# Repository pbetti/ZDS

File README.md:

# ZDS

What you find here are all my stuff about Nuova Elettronica Z80. Software, ideas &amp; projects, both software and hardware.
See more at http://www.z80cpu.eu/projects/14-data-articles/116-z80ne-where-it-all-began

Microcomputer Z80 by Nuova Elettronica

The system consists of dedicated boards. Each card performs a specific function and all the main boards are connected on a propietary bus.
As i found out later, the original design of the system was effectively developed by a company called Micro Design of Genoa and not by Nuova Elettronica.
The orientation however, is to provide an educational system as evidenced by the basic system that consists of the CPU board and an hexadecimal keyboard.
The magazine, however, has introduced later a comprehensive set of additional hardware to allow the construction of a complete system of a level comparable to systems like S-100s or TRS-80 just for an example.
The kits provided by Nuova Elettronica were presented fairly quickly at the beginning and then slow down over time.
The whole system is developed, however, covering a period of considerably long time from 1979 to 1985, which is much greater in life expectancy then today's PC.
The decision to break up the presentation and furniture of the Z80NE hardware, worked well for both the magazine, interested in selling kits and so to maintains high the interest in his system, both for the users who can spread over time the costs (quite remarkable at the end) of buying the whole system and, at the same time, having the time to "assimilate" what the magazine continues to offer in terms of didactic information a kit after another.

The board design is sophisticated and robust, with low component density so to put even the less "technically savvy" people able to mount the components without errors (well... almost).
As to be noticed, not all the hardware presented can be used simultaneously, for example, there are two video interfaces, a low resolution and a hi-res which are mutually incompatible, as well as various memory cards that can only be used in certain configurations to obtain a maximum of up to 56K of RAM which is the limit for our computer. This is because the upper 4kbytes are used by the monitor and lower 4k of RAM (a single kbyte used actually) from E000H to EFFFH is reserved for the lo-res video card.
Another interesting case is the system monitor originally present on the CPU board, which maps 1kb of EPROM at address 8000H, thus blocking any expansion above 32k, chip that infact was removed almost immediately, and placed on the floppy interface card (mapped at F000H).

This apparent schizophrenic design is explained, over the time, with the intent to have a system that users can set up accordingly to their needs and interests.
Even if, i'm willing to bet that the most of them have brought their Z80NE to its maximum potential.
Many of these limitations can easily be overcome with small interventions, as we'll see later.

The system BUS is parallel, consisting of 48 lines divided on two single-in-line connectors of 24 pins each.
The connector "A" drives power (-12V, + 12V, + 5V) and all control signals of Z80 cpu including IEI, IEO pins that should established a daisy-chain interrupt priority between the cards according to the position of insertion, feature never used by Nuova Elettronica, while the connector "B" was dedicated to the address and data lines.

Normally, the power supply and the boards were enclosed in a 5U rack mount black case. This all-black style led me to give to my system the nickname of Z80Darkstar, for which you'll find references in the next articles.

For all details about every board and also original schematics and magazine articles, please, look here: http://www.z80ne.com/eng/hardware.asp

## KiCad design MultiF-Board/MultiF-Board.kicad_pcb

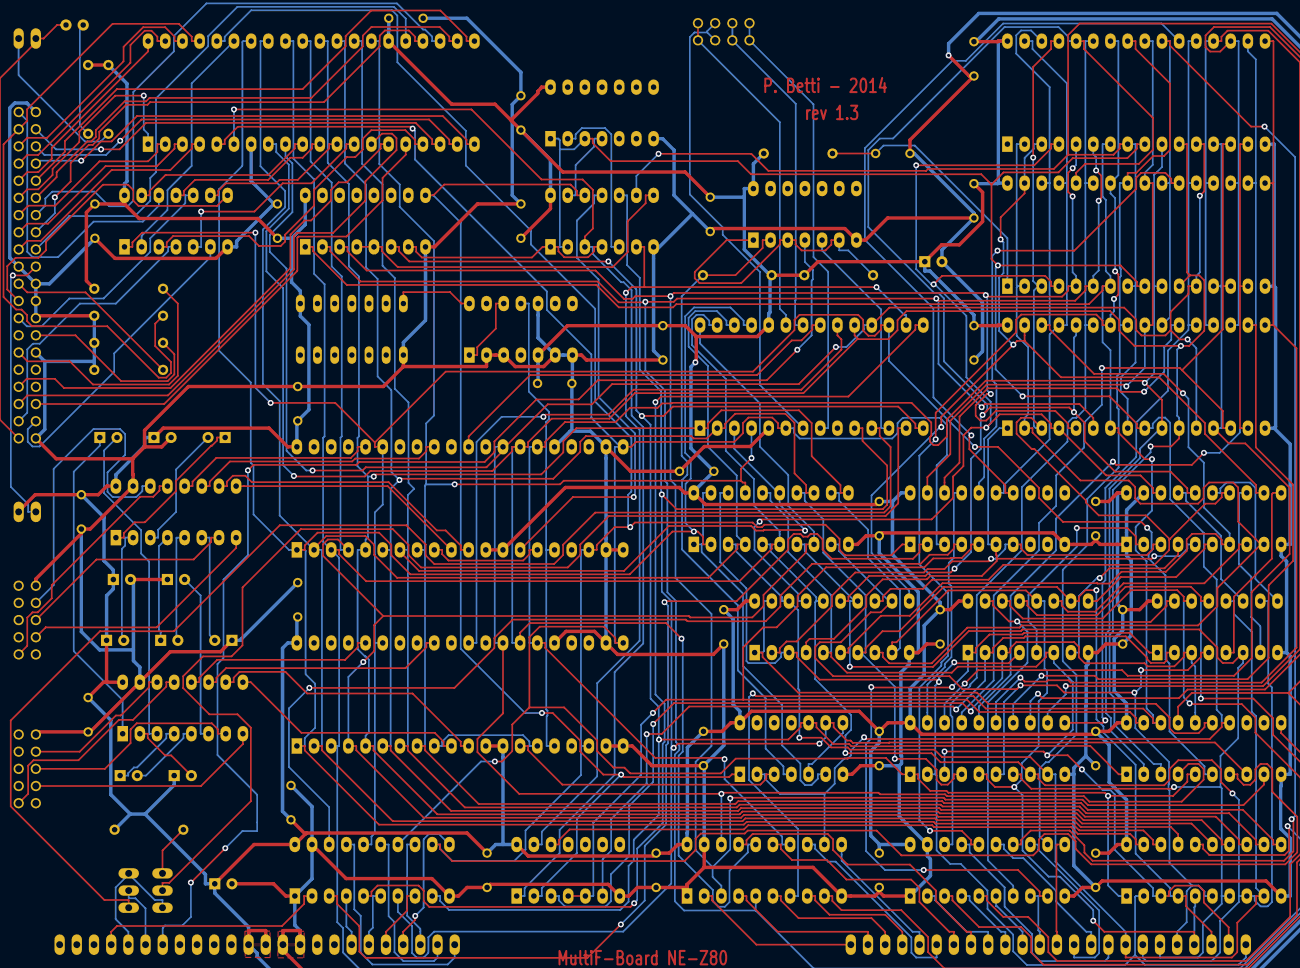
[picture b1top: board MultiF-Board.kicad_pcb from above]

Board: 2 copper layers, 93 parts (0 on the bottom side), 198 nets.

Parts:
C1, C2, C3, C4, C5, C6, C7, C8, C9, C10: 1.0 uF; C1V8
C11, C42: 10 uF; C1V8
C12, C13, C14, C15, C16, C17, C18, C19, C20, C21, C22, C23, C24, C25, C26, C27, C28, C29, C30, C31, C32, C33, C34, C35, C36, C37, C38, C39, C40: 0.1; C2
C41: 0.047; C2
D1: IDE_LED; LED-3MM
JP1, JP2: PINHD-1X3; pinhead-1-1X03
JP3: IDE_VCC; pinhead-1-1X02
JP5: PINHD-2X4; pinhead-1-2X04
JPA1: PINHD-1X24; pinhead-1-1X24
JPB1: PINHD-1X24; pinhead-1-1X24
P1: SERIAL1; pinhead-1-2X05
P2: SERIAL2; pinhead-1-2X05
P3: IDE; pinhead-1-2X20
P4: IDE_LED; pinhead-1-1X02
QG1: OSC; oldchips-DIL14
R1, R8, R9: 3300; R4
R2, R3, R4, R5: 10k; R4
R6, R7: 470; R4
R10: 330; R4
U1, U6: 74LS14; DIP-14__300_ELL
U2: 8255; DIP-40__600_ELL
U3, U4, U5, U15, U27: 74LS244; DIP-20__300_ELL
U7, U22: 74LS32; DIP-14__300_ELL
U8: 74LS11; DIP-14__300_ELL
U9, U13: 74LS245; DIP-20__300_ELL
U10: MMU_GAL; DIP-20__300_ELL
U11, U12: 7489; DIP-16__300_ELL
U14: 74LS90; DIP-14__300_ELL
U16: 74LS240; DIP-20__300_ELL
U17, U26: TI16550; DIP-40__600_ELL
U18, U21: SRAM_512K; DIP-32__600_ELL
U19: 74LS138; DIP-16__300_ELL
U20, U29: MAX-232; DIP-16__300_ELL
U23: MEM_GAL; DIP-20__300_ELL
U24: 74LS06; DIP-14__300_ELL
U25: 29EE020; DIP-32__600_ELL
U28: Z80-CTC; DIP-28__600_ELL

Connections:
+5V: C3.1, C4.1, C8.1, C9.1, C11.1, C12.1, C13.1, C14.1, C15.1, C16.1, C17.1, C18.1, C19.1, C20.1, C21.1, C22.1, C23.1, C24.1, C25.1, C26.1, C27.1, C28.1, C29.1, C30.1, C31.1, C32.1, C33.1, C34.1, C35.1, C36.1, C37.1, C38.1, C39.1, C40.1, C42.1, JP3.1, JPA1.12, JPA1.13, QG1.14, R1.1, R2.1, R6.2, R7.2, R8.2, R9.1, R10.1, U1.14, U2.26, U3.20, U4.20, U5.20, U6.14, U7.14, U8.14, U9.20, U10.20, U11.16, U12.16, U13.20, U14.5, U15.20, U16.20, U17.12, U17.13, U17.40, U18.32, U19.16, U20.16, U21.32, U22.14, U23.20, U24.14, U25.32, U26.12, U26.13, U26.40, U27.20, U28.24, U29.16
//ESR1: U17.14, U22.3
//ESR2: U7.11, U26.14
//E_CTC: U7.6, U8.13, U28.16
//E_IDE: U2.6, U7.3, U8.1
//E_SER: U7.12, U8.2, U19.9, U22.1
//IDECTC: U7.1, U7.4, U19.7
//INT: JPA1.7, U24.4
//ISR: R8.1, U22.4, U24.2
//MBUSEN: U9.19, U23.17
//MENA: U8.4, U8.5, U10.19, U23.5
//MME: U8.6, U11.2, U12.2
//MOE: U18.24, U21.24, U23.19, U25.24
//MRD: U10.15, U15.1, U15.19
//MWE: U18.29, U21.29, U23.15, U25.31
//MWR: U8.3, U10.16, U11.3, U12.3
/CSEL: P3.28, R4.2
/C_D0: U2.34, U13.18, U17.1, U26.1, U27.2, U28.25
/C_D1: U2.33, U13.17, U17.2, U26.2, U27.4, U28.26
/C_D2: U2.32, U13.16, U17.3, U26.3, U27.6, U28.27
/C_D3: U2.31, U13.15, U17.4, U26.4, U27.8, U28.28
/C_D4: U2.30, U13.14, U17.5, U26.5, U27.11, U28.1
/C_D5: U2.29, U13.13, U17.6, U26.6, U27.13, U28.2
/C_D6: U2.28, U13.12, U17.7, U26.7, U27.15, U28.3
/C_D7: U2.27, U13.11, U17.8, U26.8, U27.17, U28.4
/C_IEI: JP1.2, U28.13
/C_IEO: JP2.1, U28.11
/DMARQ: P3.21, R5.2
/DSR1: P1.2, U20.13
/DSR2: P2.2, U29.13
/DTR1: P1.7, U20.14
/DTR2: P2.7, U29.14
/IDE_VCC: JP3.2, P3.20
/IORQ: U3.7, U7.10, U10.8, U22.9, U28.10
/IRQ1: U17.30, U28.20
/IRQ2: U26.30, U28.21
/M1: U3.9, U10.1, U19.6, U22.10, U28.14
/MA12: U15.17, U16.18, U18.4, U21.4, U25.4
/MA13: U15.15, U16.16, U18.28, U21.28, U25.28
/MA14: U15.13, U16.14, U18.3, U21.3, U25.29
/MA15: U15.11, U16.12, U18.31, U21.31, U25.3
/MA16: U15.8, U16.9, U18.2, U21.2, U25.2
/MA17: U15.6, U16.7, U18.30, U21.30, U25.30
/MA18: U15.4, U16.5, U18.1, U23.6
/MA19: U15.2, U16.3, U23.7
/MD0: U9.18, U18.13, U21.13, U25.13
/MD1: U9.17, U18.14, U21.14, U25.14
/MD2: U9.16, U18.15, U21.15, U25.15
/MD3: U9.15, U18.17, U21.17, U25.17
/MD4: U9.14, U18.18, U21.18, U25.18
/MD5: U9.13, U18.19, U21.19, U25.19
/MD6: U9.12, U18.20, U21.20, U25.20
/MD7: U9.11, U18.21, U21.21, U25.21
/MPUP: C41.1, R10.2, U21.1
/MREQ: U3.3, U23.2
/PA0: P3.17, U2.4
/PA1: P3.15, U2.3
/PA2: P3.13, U2.2
/PA3: P3.11, U2.1
/PA4: P3.9, U2.40
/PA5: P3.7, U2.39
/PA6: P3.5, U2.38
/PA7: P3.3, R3.2, U2.37
/PB0: P3.4, U2.18
/PB1: P3.6, U2.19
/PB2: P3.8, U2.20
/PB3: P3.10, U2.21
/PB4: P3.12, U2.22
/PB5: P3.14, U2.23
/PB6: P3.16, U2.24
/PB7: P3.18, U2.25
/PC0: P3.35, U2.14
/PC1: P3.33, U2.15
/PC2: P3.36, U2.16
/PC3: U1.3, U2.17
/PC4: U1.5, U2.13
/PC5: U1.9, U2.12
/PC6: U1.11, U2.11
/PC7: U1.13, U2.10
/RD: U2.5, U3.14, U9.1, U10.5, U13.1, U17.21, U23.3, U26.21, U28.6
/RFH: U3.18, U23.4
/RST: U1.1, U3.16, U10.6, U17.35, U26.35, U28.17
/RX1: P1.3, U20.8
/RX2: P2.3, U29.8
/SER_CLK: U14.11, U17.16, U26.16
/T0: JP5.1, JP5.2, U28.23
/T1: JP5.5, JP5.6, U28.22
/TX1: P1.5, U20.7
/TX2: P2.5, U29.7
/WR: U2.36, U3.12, U10.7, U17.18, U23.1, U26.18
/Z0: JP5.3, JP5.4, U28.7
/Z1: JP5.7, JP5.8, U28.8
/~ACTIVE: D1.2, P3.39, P4.2
/~DMACK: P3.29, R2.2
/~PC3: P3.37, U1.4
/~PC4: P3.38, U1.6
/~PC5: P3.23, U1.8
/~PC6: P3.25, U1.10
/~PC7: P3.1, U1.12
A0: U2.9, U4.18, U10.4, U17.28, U18.12, U21.12, U25.12, U26.28, U28.18
A1: U2.8, U4.16, U10.3, U17.27, U18.11, U21.11, U25.11, U26.27, U28.19
A2: U4.14, U10.2, U17.26, U18.10, U21.10, U25.10, U26.26
A3: U4.12, U6.1, U6.3, U7.2, U10.14, U18.9, U21.9, U22.2, U25.9
A4: U4.9, U7.9, U10.17, U18.8, U21.8, U25.8
A5: U4.7, U10.18, U18.7, U19.1, U21.7, U25.7
A6: U4.5, U10.11, U18.6, U19.2, U21.6, U25.6
A7: U4.3, U10.9, U18.5, U19.3, U21.5, U25.5
A8: U5.18, U18.27, U21.27, U25.27
A9: U5.16, U18.26, U21.26, U25.26
A10: U5.14, U18.23, U21.23, U25.23
A11: U5.12, U18.25, U21.25, U25.25
A12: U5.9, U11.1, U12.1
A13: U5.7, U11.15, U12.15
A14: U5.5, U11.14, U12.14
A15: U5.3, U11.13, U12.13
CLK: U3.5, U28.15
D0: JPB1.24, U9.2, U11.4, U13.2, U15.3, U27.18
D1: JPB1.23, U9.3, U11.6, U13.3, U15.5, U27.16
D2: JPB1.22, U9.4, U11.10, U13.4, U15.7, U27.14
D3: JPB1.21, U9.5, U11.12, U13.5, U15.9, U27.12
D4: JPB1.20, U9.6, U12.4, U13.6, U15.12, U27.9
D5: JPB1.19, U9.7, U12.6, U13.7, U15.14, U27.7
D6: JPB1.18, U9.8, U12.10, U13.8, U15.16, U27.5
D7: JPB1.17, U9.9, U12.12, U13.9, U15.18, U27.3
GND: C4.2, C5.1, C9.2, C10.1, C11.2, C12.2, C13.2, C14.2, C15.2, C16.2, C17.2, C18.2, C19.2, C20.2, C21.2, C22.2, C23.2, C24.2, C25.2, C26.2, C27.2, C28.2, C29.2, C30.2, C31.2, C32.2, C33.2, C34.2, C35.2, C36.2, C37.2, C38.2, C39.2, C40.2, C41.2, C42.2, JPA1.14, JPA1.15, P1.9, P2.9, P3.2, P3.19, P3.22, P3.24, P3.26, P3.30, P3.40, QG1.7, R3.1, R4.1, R5.1, U1.7, U2.7, U3.1, U3.10, U3.19, U4.1, U4.10, U4.19, U5.1, U5.10, U5.19, U6.7, U7.7, U8.7, U9.10, U10.10, U11.8, U12.8, U13.10, U14.2, U14.3, U14.6, U14.7, U14.10, U15.10, U16.1, U16.10, U16.19, U17.19, U17.20, U17.22, U17.25, U18.16, U19.8, U20.15, U21.16, U22.7, U23.10, U24.7, U25.16, U26.19, U26.20, U26.22, U26.25, U27.10, U28.5, U29.15
unnamed: U6.2, U7.5
unnamed: R9.2, U24.1, U24.3, U24.6
unnamed: JP1.1, JP2.3, JPA1.5
unnamed: JP2.2, JPA1.6
unnamed: JP1.3, R1.2
unnamed: U21.22, U23.16
unnamed: JPB1.15, U5.15
unnamed: JPB1.16, U5.17
unnamed: U22.5, U22.8
unnamed: U22.6, U27.1, U27.19
unnamed: C6.2, U29.3
unnamed: C6.1, U29.1
unnamed: C7.1, U29.4
unnamed: C8.2, U29.2
unnamed: C7.2, U29.5
unnamed: U26.32, U29.11
unnamed: C5.2, U20.6
unnamed: U26.11, U29.10
unnamed: U26.10, U29.9
unnamed: C10.2, U29.6
unnamed: U26.36, U29.12
unnamed: U26.9, U26.15
unnamed: U24.5, U28.12
unnamed: U8.12, U13.19
unnamed: U7.8, U19.4, U19.5
unnamed: U6.4, U7.13
unnamed: JPA1.4, U3.2
unnamed: U17.9, U17.15
unnamed: U14.1, U14.12
unnamed: U1.2, U2.35
unnamed: QG1.8, U14.14
unnamed: U17.36, U20.12
unnamed: U17.32, U20.11
unnamed: U17.10, U20.9
unnamed: U17.11, U20.10
unnamed: JPA1.20, U3.8
unnamed: JPA1.21, U3.11
unnamed: JPA1.22, U3.13
unnamed: JPA1.23, U3.15
unnamed: JPA1.24, U3.17
unnamed: U11.9, U16.6
unnamed: U11.7, U16.4
unnamed: U11.5, U16.2
unnamed: JPA1.18, U3.4
unnamed: JPA1.19, U3.6
unnamed: JPB1.6, U4.13
unnamed: JPB1.7, U4.15
unnamed: JPB1.8, U4.17
unnamed: JPB1.9, U5.2
unnamed: JPB1.10, U5.4
unnamed: JPB1.11, U5.6
unnamed: JPB1.12, U5.8
unnamed: JPB1.13, U5.11
unnamed: JPB1.14, U5.13
unnamed: JPB1.1, U4.2
unnamed: JPB1.2, U4.4
unnamed: JPB1.3, U4.6
unnamed: JPB1.4, U4.8
unnamed: JPB1.5, U4.11
unnamed: D1.1, R6.1
unnamed: P4.1, R7.1
unnamed: U18.22, U23.18
unnamed: U12.5, U16.11
unnamed: U12.7, U16.13
unnamed: U12.9, U16.15
unnamed: U12.11, U16.17
unnamed: U11.11, U16.8
unnamed: U23.14, U25.22
unnamed: C2.2, U20.5
unnamed: C2.1, U20.4
unnamed: C1.2, U20.3
unnamed: C3.2, U20.2
unnamed: C1.1, U20.1

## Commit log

2016-04-23 Force realigment
2016-04-23 Monitor sources dir reintroducted.
2016-04-24 Optimized gencpm.dat management
2016-04-25 Disk generation reorganized.
2016-05-15 Standard DRI disk images ok.
2016-05-15 Fixed z3plus bootstrap from virtual disks
2016-06-19 Explained 6545 register
2016-07-03 Rewritten CRTC management. Fixed LF/CR bug
2016-07-03 file cleanup
2016-07-17 refined floppy i/o routines. error correctly catched but cp/m 3 still hang on floppy error...
2016-08-21 Release 3.4. Fixed empty floppy drive bug. Still need reboot to see partition table.
2016-09-10 workaround for double hd initialization needed to see partitions. Revision updated to 3.5
2017-01-07 fdisk re-add
2017-01-07 Fixed fdisk to git
2017-04-03 Serial line transfer driver & software added. First version (alpha)
2017-04-03 Fixed file submission
2017-05-18 modified lx529, ep529 char map
2017-05-25 Modified LX529 character generator eproms
2017-11-14 - Almost completed ZMODEM - Start port of NEDOS Basic to CP/M - Some bug fixes
2017-11-14 fixed zmodem tree
2017-11-24 Git branch alignment
2017-12-16 Added dsktran utility, heavy modifications to vdsk_server, initial support for NEDOS, added eprom loaders
2017-12-16 Removed dsktran directory
2018-01-18 Added support dir for external but mandatory tools/libs
2018-03-21 vdsk_server fixing on IMD support. New version 1.8.1
2018-08-15 New version of trampoline
2018-08-16 Standard char print moved in common area to improve speed (no bank switch)
2018-08-16 Fixed new compact trampoline. THIS REQUIRE COMPLETE SW REBUILD.
2018-08-25 - optimized CP/M3 - inserted emdedded debugger for CP/M3 bios - fixed time module bug
2018-08-26 CP/M3 size optimization fix on vdsk_server for skew == 0
2018-08-29 fixed old bug on serial console (data loss on transfer)
2018-08-29 renamed s -> s.static tp recover Udo Munk's git version
2018-08-30 Initial commit for v 4.0.0
2018-08-31 added eeprom programmer as stand alone prog. "flasher"
2018-09-08 v 3.9.2
2018-09-08 zipped vi
2018-09-08 rom image management rewritten
2018-09-13 v3.9.4 fixed serial console for new features
2018-09-20 v3.9.7
2018-09-27 fdisk 1.1, MultiF-Board schematic upgrade
2018-09-30 sdcc cp/m io low level support
2018-10-09 Added CP/M support stdio library for sdcc
2018-11-06 rel 4.0.0
2018-11-07 flasher bug fixed
2018-12-06 Recovered ROM basic
2019-01-03 Porting of Rogue game
2019-02-06 Pre support dual IDE
2019-02-17 v5.0.0 running 32k sysbios
2019-03-11 Dual IDE support in sysbios
2019-03-13 fixing CP/M bugs on new sysbios
2019-03-15 DBG on CP/M
2019-03-31 dual ide CP/M bug fixed
2019-04-14 Dual IDE completed
2019-04-15 Fixed CP/M bug for large cpm3.sys - Mapped 16 drives
2019-04-19 Cleanup
2019-04-29 CF Card support and HD I: image init
2019-04-29 missing cf_init
2019-05-01 Master/slave option for cf_init
2019-05-02 v5.0.1
2019-05-02 fix 5.0.1
2019-05-03 immagine eeprom
2019-05-27 Fixed (probably) cold boot video init. Parallel 2.0 support by default.
2019-07-27 git tree reorg, mbasic project started
2019-07-27 git reorg
2019-07-27 git cleanup
2020-08-25 new work merge
2020-10-16 VGA alt
2020-10-22 replaced with a working copy
    Got from the Z80NE CP/M disk images.
    First pass: disk image converted to RAW with IMDU
    Seconf pass: cpmtools, by adjusting the 'skew' parameter on 'diskdefs' as follows
    diskdef SONE128
    seclen 128
    tracks 40
2020-10-22 More files from Z80NE CP/M disks
